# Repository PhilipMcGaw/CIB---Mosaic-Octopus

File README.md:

# CIB - Mosaic Octopus

Breakout board for Pico Technologies Ltd ADC20/ADC24 (https://www.picotech.com/accessories/data-logger-terminal-boards/adc-20-24-terminal-board)

> The ADC-20/ADC-24 Terminal Board is designed for use with the 8-channel ADC-20 and 16-channel ADC-24 High-Resolution Data Loggers. For simple applications, you can simply connect sensor wires to the screw terminals on the terminal board without the need for soldering. For more advanced applications, the terminal board enables you to design and build sensor circuits that condition measurements for the data loggers to process. The board has empty locations for extra components.

## Pinout

| DB 25 Pin (J1) | Function |
| --- | --- |
| 1  | Analogue Channel 2 |
| 2  | Analogue Channel 4 |
| 3  | Analogue Channel 6 |
| 4  | Analogue Channel 8 |
| 5  | Analogue Channel 10 |
| 6  | Analogue Channel 12 |
| 7  | Analogue Channel 14 |
| 8  | Analogue Channel 16 |
| 9  | Analogue Ground (AG) |
| 10 | +5 VDC |
| 11 | -5 VDC |
| 12 | +2V5 |
| 13 | DIO 4 |
| 14 | Analogue Channel 1 |
| 15 | Analogue Channel 3 |
| 16 | Analogue Channel 5 |
| 17 | Analogue Channel 7 |
| 18 | Analogue Channel 9 |
| 19 | Analogue Channel 11 |
| 20 | Analogue Channel 13 |
| 21 | Analogue Channel 15 |
| 22 | Digital Ground (DG) |
| 23 | DIO 1 |
| 24 | DIO 2 |
| 25 | DIO 3 |

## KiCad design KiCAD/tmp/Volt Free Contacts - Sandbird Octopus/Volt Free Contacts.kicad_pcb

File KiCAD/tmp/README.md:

# Cephalopds

## Breakout PCBs

| | Labjack T7 | DAQM901A (20 channel Mux) | DAQM903A (20 channel relay card) | DAQM907A (mutifucntion card) | DAQM908A (40 channel single ended mux) |
| ---- | ----- | ---- |-----| ------ | ----- | ----- | 
| Blanket Octopus -- DE9 Breakout PCB |
| Algae Octopus -- DA15 Breakout PCB | 1x |    |   | |  |
| Bimac Octopus - DB25 Breakout PCB | | 2x | 1x |  |  |
| Coconut Octopus - DC37 Breakout PCB | 1 x| | 1x | 1x | 2 x |
|Flapjack Octopus -- Labjack T7 Breakout | 1 x|

### Flapjack Octopus -- Labjack T7 Breakout

[Flapjack Octopus -- Labjack T7 Breakout](https://chargepoint.atlassian.net/wiki/spaces/EN/pages/5075305172/Labjack+T7+Breakout+-+Flapjack+Octopus)

This is a breakout PCB for a Labjack T7, with 2.5 mm pitch screw headers to allow for quick wiring to the breakout PCB.

  * Digital IO ports are 5 V tolerant, there is no additional protection on the PCB.
  * Digital IO on ports C, E, F and M each have an LED that illuminates when 5V DC is applied
  * Digital IO port F is also set up as eight relay outputs, allowing up to eight 12/24 V (separate power supply required) to be driven from the Labjack
  * Analogue in ports are taken via a potential divider to allow prescaling if required.
  * Additional terminals are available for 5V and Ground, as well as other pins, these are on the lower edge. 

### Blanket Octopus -- DE9 Breakout PCB

[Blanket Octopus - DE9 Breakout PCB](https://chargepoint.atlassian.net/wiki/spaces/EN/pages/5095228149/DE9+Breakout+PCB+-+Blanket+Octopus)

### Algae Octopus -- DA15 Breakout PCB

[Algae Octopus - DA15 Breakout PCB](https://chargepoint.atlassian.net/wiki/spaces/EN/pages/5095195307/DA15+Breakout+PCB+-+Algae+Octopus)

### Bimac Octopus -- DB25 Breakout PCB

[Bimac Octopus - DB25 Breakout PCB](https://chargepoint.atlassian.net/wiki/spaces/EN/pages/5094773639/DB25+Breakout+PCB+-+Bimac+Octopus)

This is the breakout for a DB25 D-type, two of these are used to interface with the DAQ970's DAQM901A module, and one for the DAQM903A card.

### Coconut Octopus -- DC37 Breakout PCB

[Coconut Octopus - DC37 Breakout PCB](https://chargepoint.atlassian.net/wiki/spaces/EN/pages/5094741845/DC37+Breakout+PCB+-+Coconut+Octopus)

This is the breakout for a DC37 D-type, two of these are used to interface with the DAQ970's DAQM908A module, one for the DAQM903A  and one for the DAQM907A card,

## Simulation PCBs

### Pygmy Octopus -- RTD Simulation

[Pygmy Octopus - RTD Simulator](https://chargepoint.atlassian.net/wiki/spaces/EN/pages/5094740380/PT100+Simulator+-+Pygmy+Octopus)

### Sandbird Octopus -- Volt Free Contacts

[Sandbird Octopus - Volt Free Contacts](https://chargepoint.atlassian.net/wiki/spaces/EN/pages/5095260299/Volt+Free+Contacts+-+Sandbird+Octopus)

### Star-Sucker Pygmy Octopus -- Fans, Pumps and other loads

[Star-Sucker Pygmy Octopus - Fans, Pumps and other loads](https://chargepoint.atlassian.net/wiki/spaces/EN/pages/5129112107/Fans+Pumps+and+other+loads+-+Star-Sucker+Pygmy+Octopus)

### Blanket Octopus -- Relay / Contactor board

[Blanket Octopus -- Relay / Contactor board](https://chargepoint.atlassian.net/wiki/spaces/EN/pages/5129242298/Relay+Contactor+board+-+Blanket+Octopus)

--

Giant Pacific Octopus
Dumbo Octopus
California Two-Spot Octopus

Mimic Octopus
[Atlantic] Pygmy Octopus
Common Octopus

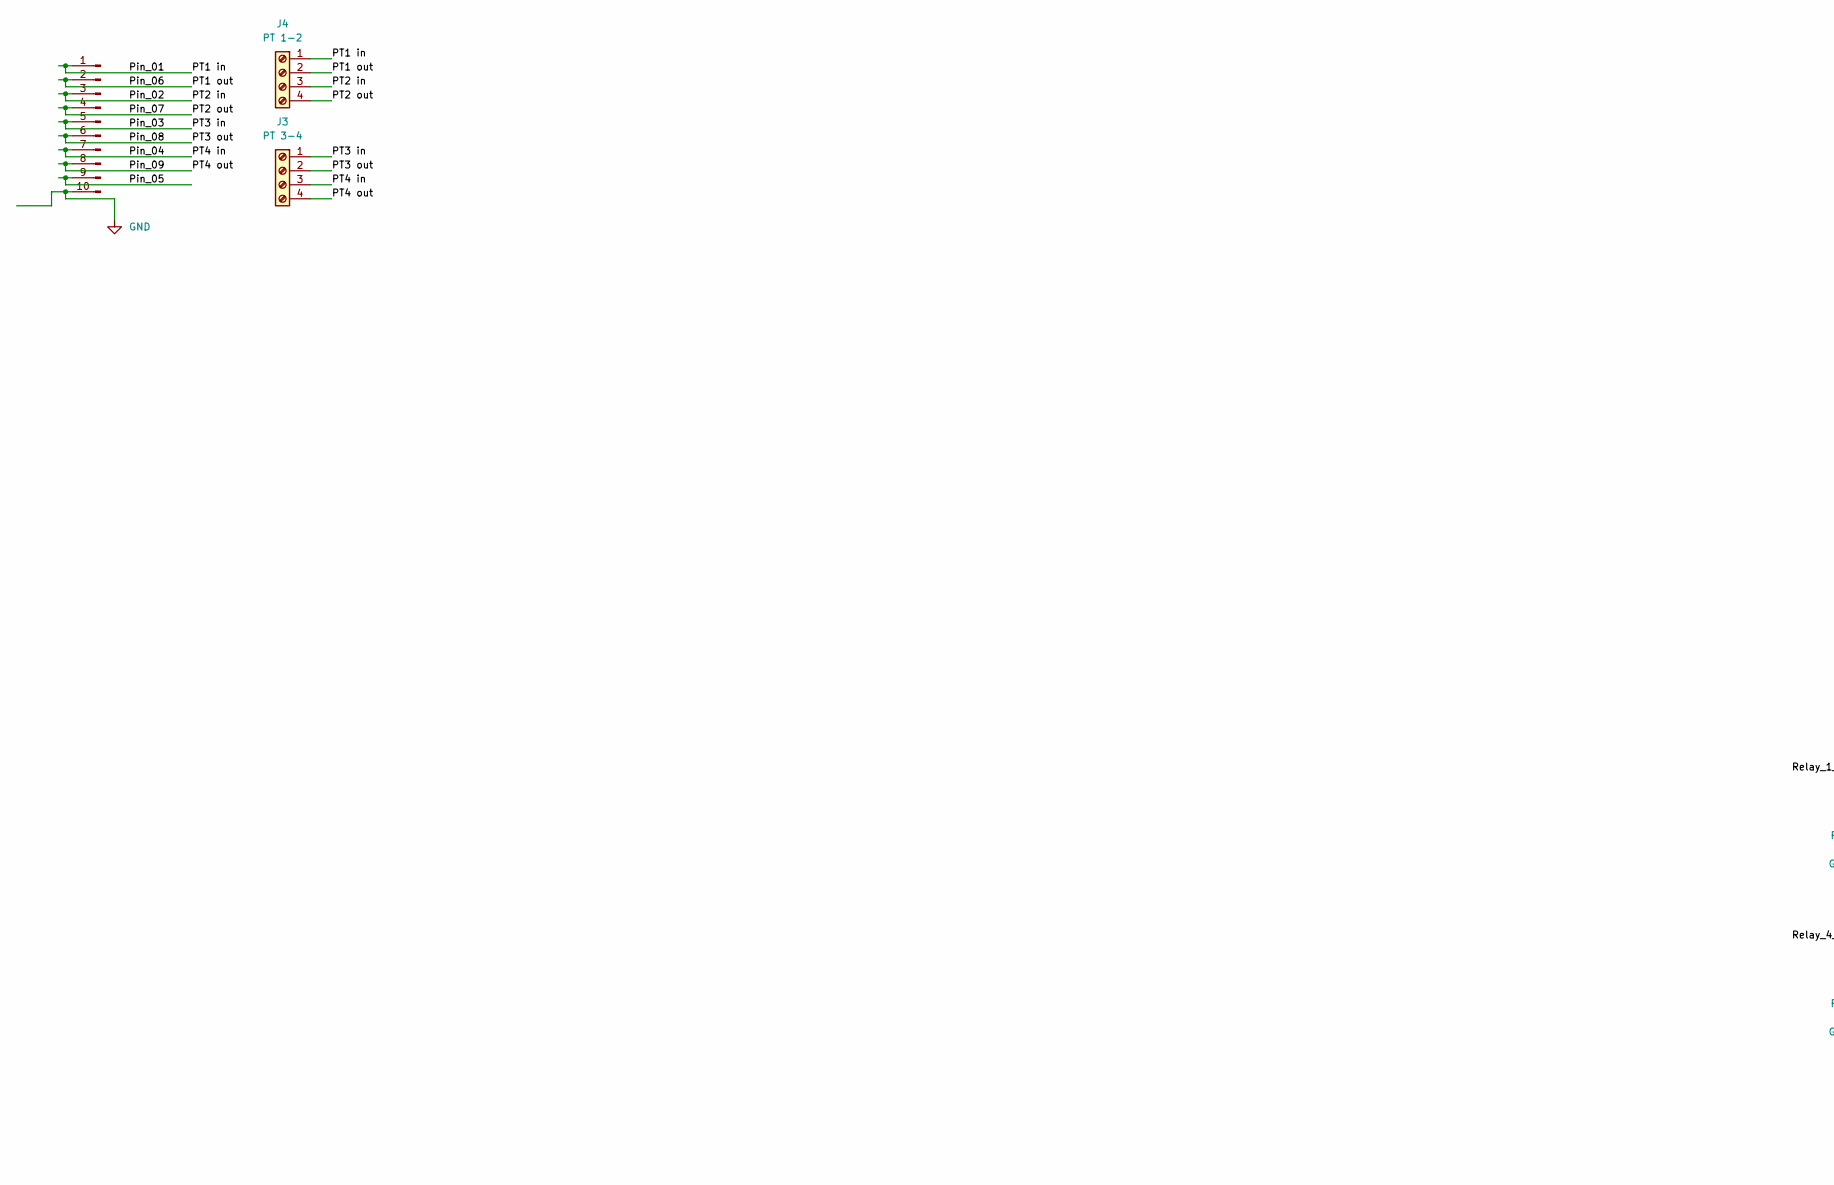
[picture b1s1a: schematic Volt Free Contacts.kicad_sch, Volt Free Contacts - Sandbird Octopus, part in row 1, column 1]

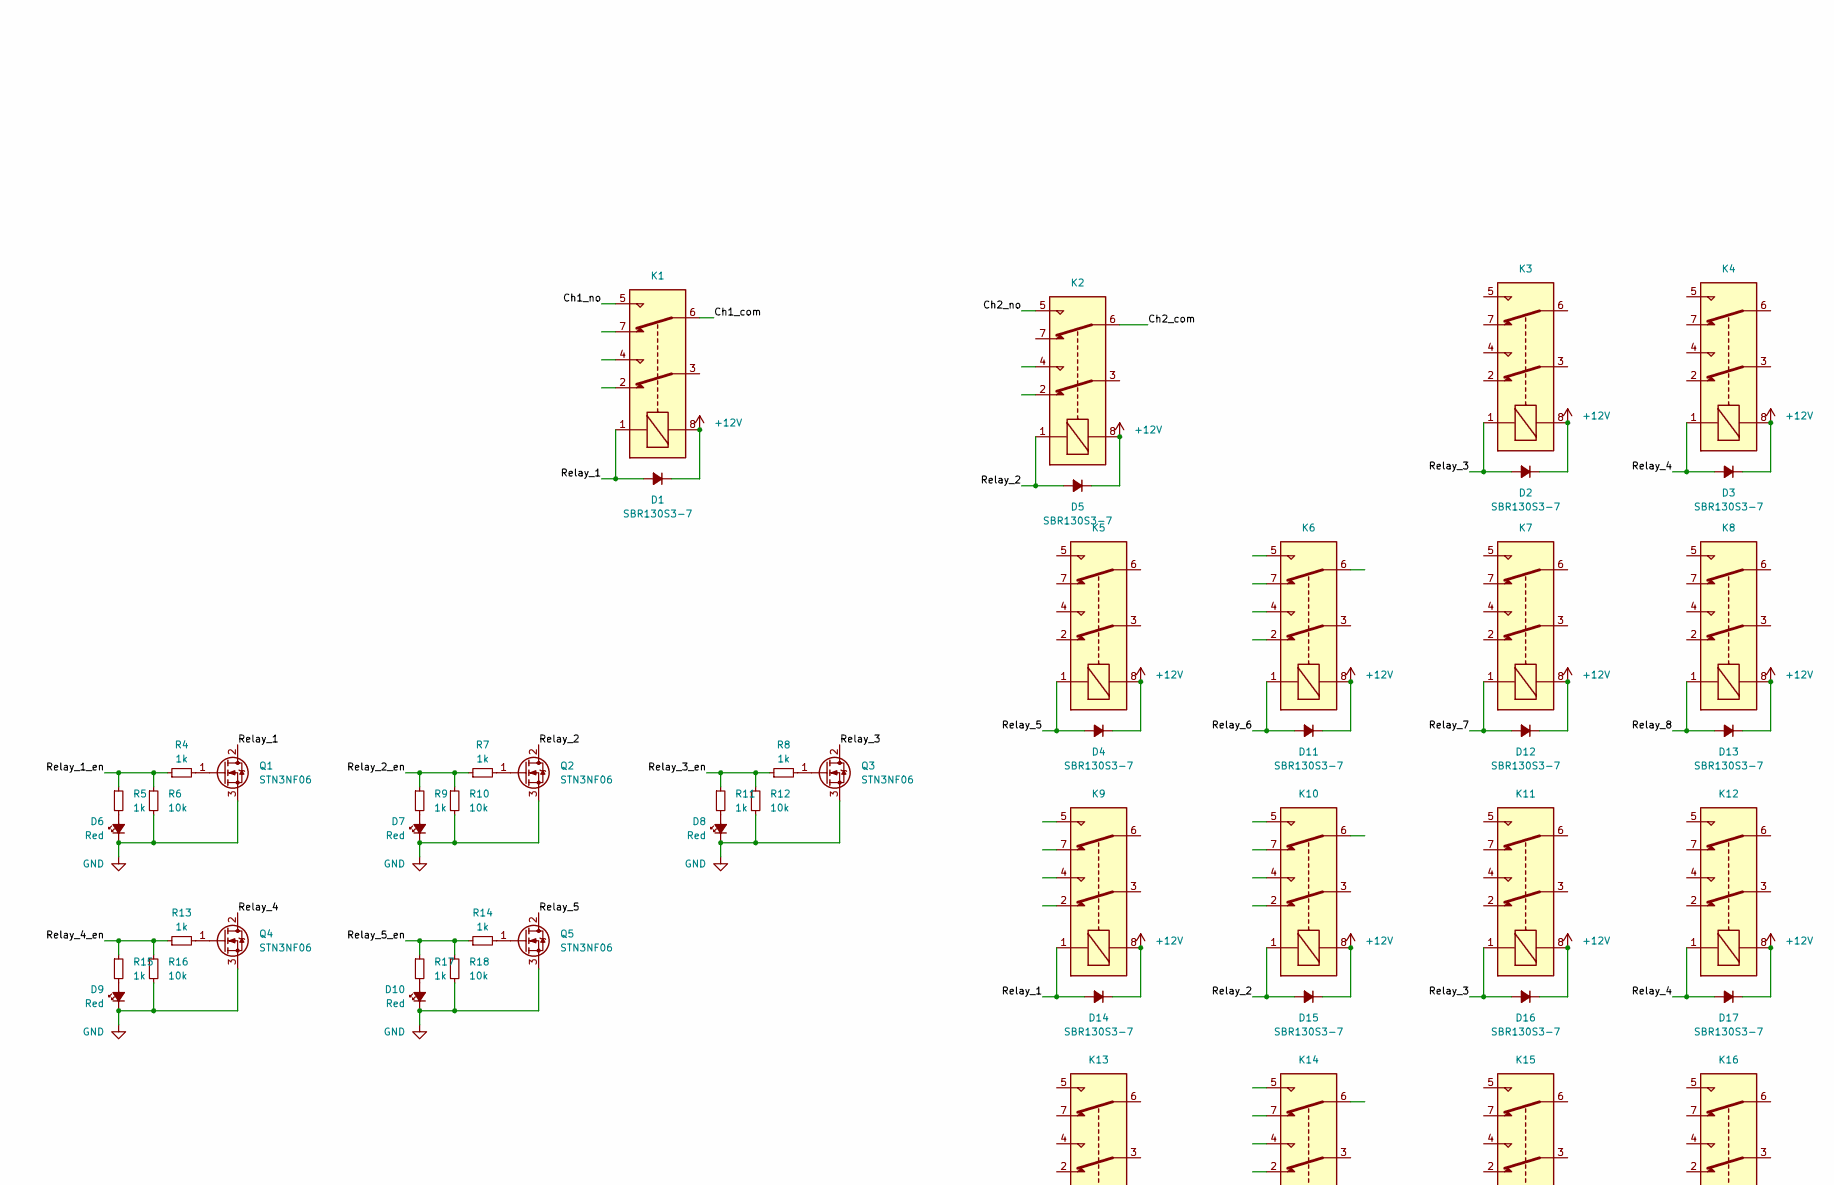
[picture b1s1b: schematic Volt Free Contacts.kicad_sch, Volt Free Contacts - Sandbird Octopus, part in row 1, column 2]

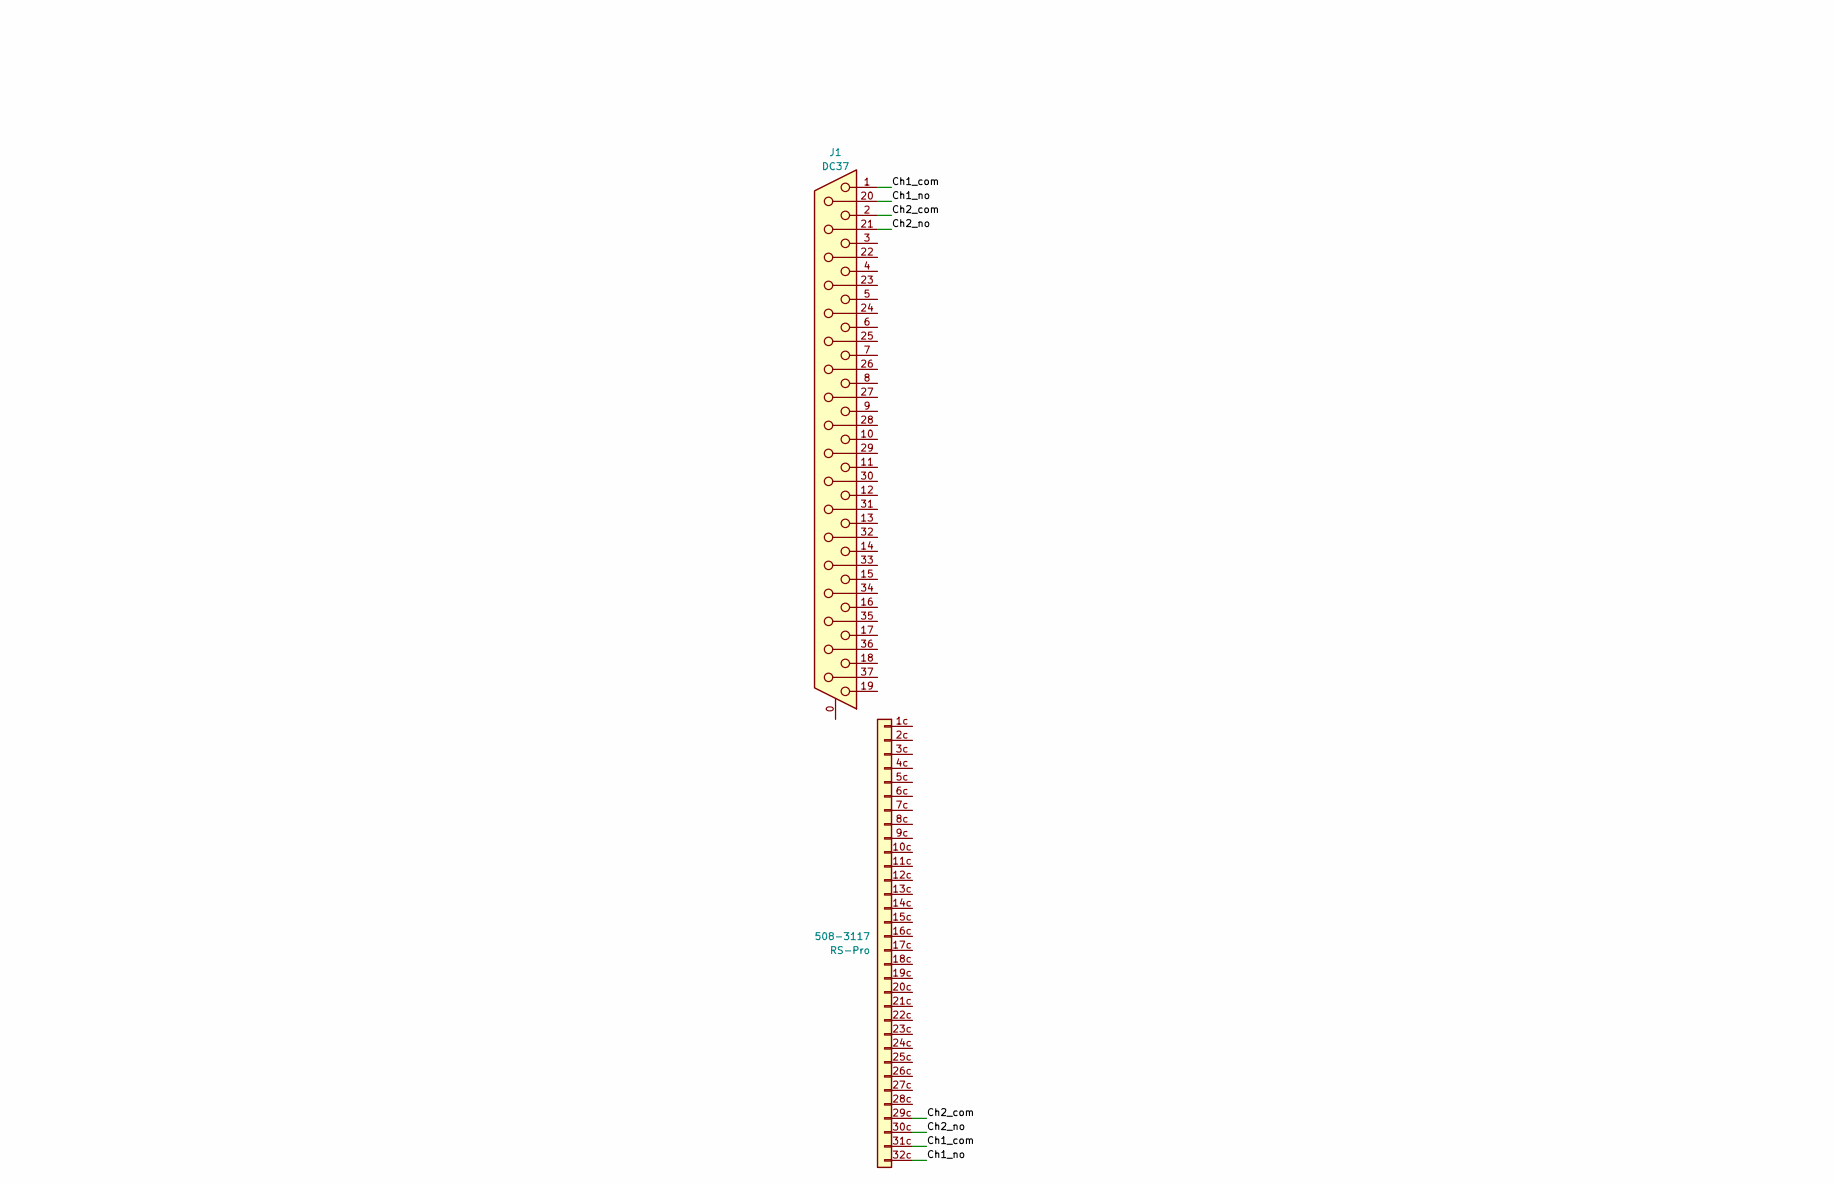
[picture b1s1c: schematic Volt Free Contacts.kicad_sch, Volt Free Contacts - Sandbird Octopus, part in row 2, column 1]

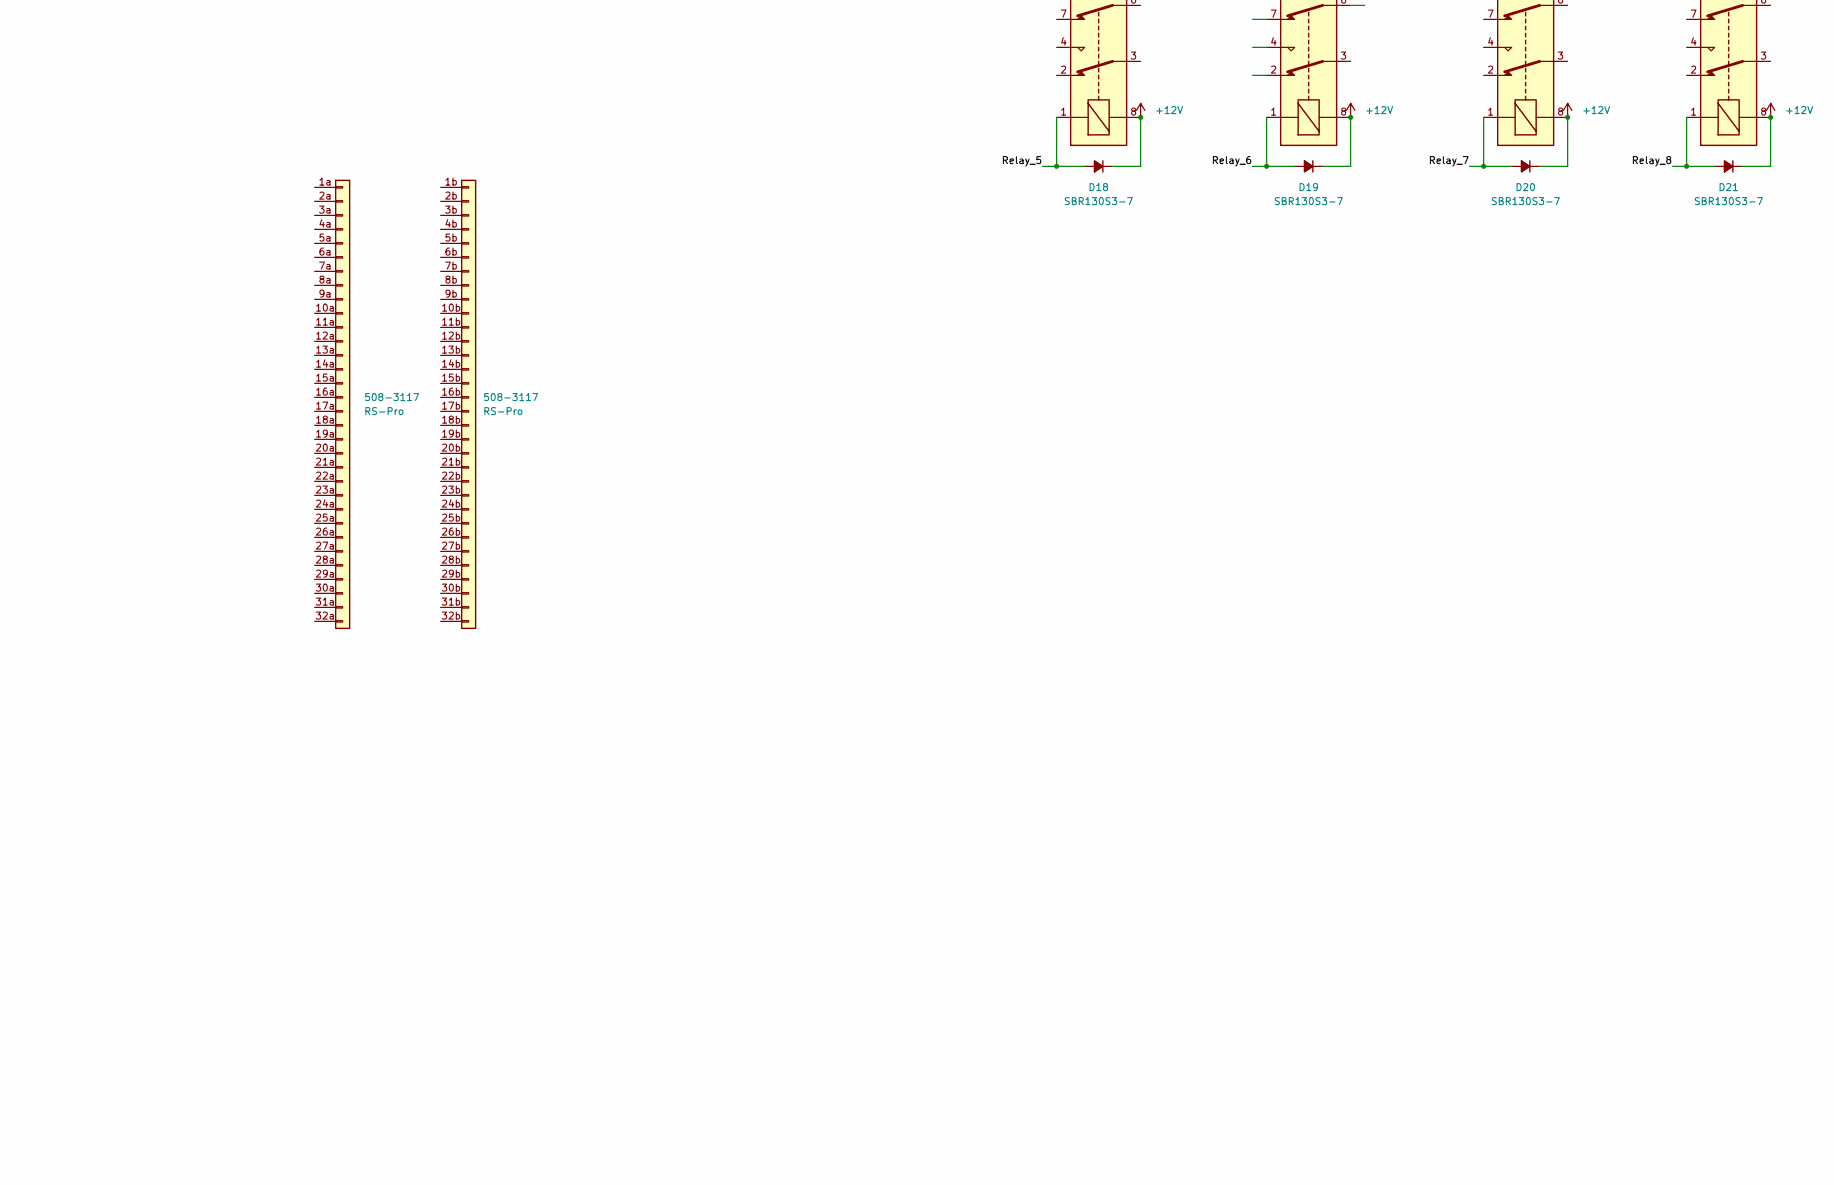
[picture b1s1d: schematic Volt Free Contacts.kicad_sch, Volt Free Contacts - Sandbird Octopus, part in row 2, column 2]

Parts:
D1, D2, D3, D4, D5, D11, D12, D13, D14, D15, D16, D17, D18, D19, D20, D21: SBR130S3-7; D_SOD-323_HandSoldering
D6, D7, D8, D9, D10: Red; LED_0805_2012Metric_Pad1.15x1.40mm_HandSolder
J1: DC37; DSUB-37_Female_Horizontal_P2.77x2.84mm_EdgePinOffset9.90mm_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
J3: PT 3-4; TerminalBlock_Phoenix_MPT-0,5-4-2.54_1x04_P2.54mm_Horizontal
J4: PT 1-2; TerminalBlock_Phoenix_MPT-0,5-4-2.54_1x04_P2.54mm_Horizontal
J6: Pin Header; PinHeader_2x05_P2.54mm_Vertical
J7: 03x32_DIN41612; Eurocard; Manufacture PartNumber 508-3117
K1, K2, K3, K4, K5, K6, K7, K8, K9, K10, K11, K12, K13, K14, K15, K16: Relay_DPDT_Omron_G6K-2P; Manufacturer # G6K-2P DC12; DigiKey # Z117-ND
Q1, Q2, Q3, Q4, Q5: STN3NF06; SOT-223-3_TabPin2
R4, R5, R7, R8, R9, R11, R13, R14, R15, R17: 1k; R_0805_2012Metric_Pad1.20x1.40mm_HandSolder
R6, R10, R12, R16, R18: 10k; R_0805_2012Metric_Pad1.20x1.40mm_HandSolder

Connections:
+12V: D1.1 (K), D2.1 (K), D3.1 (K), D4.1 (K), D5.1 (K), D11.1 (K), D12.1 (K), D13.1 (K), D14.1 (K), D15.1 (K), D16.1 (K), D17.1 (K), D18.1 (K), D19.1 (K), D20.1 (K), D21.1 (K), K1.8, K2.8, K3.8, K4.8, K5.8, K6.8, K7.8, K8.8, K9.8, K10.8, K11.8, K12.8, K13.8, K14.8, K15.8, K16.8
/Ch1_com: J1.1, J7.31c (Pin_31), K1.6
/Ch1_no: J1.20, J7.32c (Pin_32), K1.5
/Ch2_com: J1.2, J7.29c (Pin_29), K2.6
/Ch2_no: J1.21, J7.30c (Pin_30), K2.5
/PT1 in: J4.1, J6.1
/PT1 out: J4.2, J6.2
/PT2 in: J4.3, J6.3
/PT2 out: J4.4, J6.4
/PT3 in: J3.1, J6.5
/PT3 out: J3.2, J6.6
/PT4 in: J3.3, J6.7
/PT4 out: J3.4, J6.8
/Pin_05: J6.9
/Relay_1: D1.2 (A), D14.2 (A), K1.1, K9.1, Q1.2 (D)
/Relay_1_en: R4.1, R5.1, R6.1
/Relay_2: D5.2 (A), D15.2 (A), K2.1, K10.1, Q2.2 (D)
/Relay_2_en: R7.1, R9.1, R10.1
/Relay_3: D2.2 (A), D16.2 (A), K3.1, K11.1, Q3.2 (D)
/Relay_3_en: R8.1, R11.1, R12.1
/Relay_4: D3.2 (A), D17.2 (A), K4.1, K12.1, Q4.2 (D)
/Relay_4_en: R13.1, R15.1, R16.1
/Relay_5: D4.2 (A), D18.2 (A), K5.1, K13.1, Q5.2 (D)
/Relay_5_en: R14.1, R17.1, R18.1
/Relay_6: D11.2 (A), D19.2 (A), K6.1, K14.1
/Relay_7: D12.2 (A), D20.2 (A), K7.1, K15.1
/Relay_8: D13.2 (A), D21.2 (A), K8.1, K16.1
GND: D6.1 (K), D7.1 (K), D8.1 (K), D9.1 (K), D10.1 (K), J6.10, Q1.3 (S), Q2.3 (S), Q3.3 (S), Q4.3 (S), Q5.3 (S), R6.2, R10.2, R12.2, R16.2, R18.2
unnamed: D6.2 (A), R5.2
unnamed: D7.2 (A), R9.2
unnamed: D8.2 (A), R11.2
unnamed: D9.2 (A), R15.2
unnamed: D10.2 (A), R17.2
unnamed: Q1.1 (G), R4.2
unnamed: Q2.1 (G), R7.2
unnamed: Q3.1 (G), R8.2
unnamed: Q4.1 (G), R13.2
unnamed: Q5.1 (G), R14.2

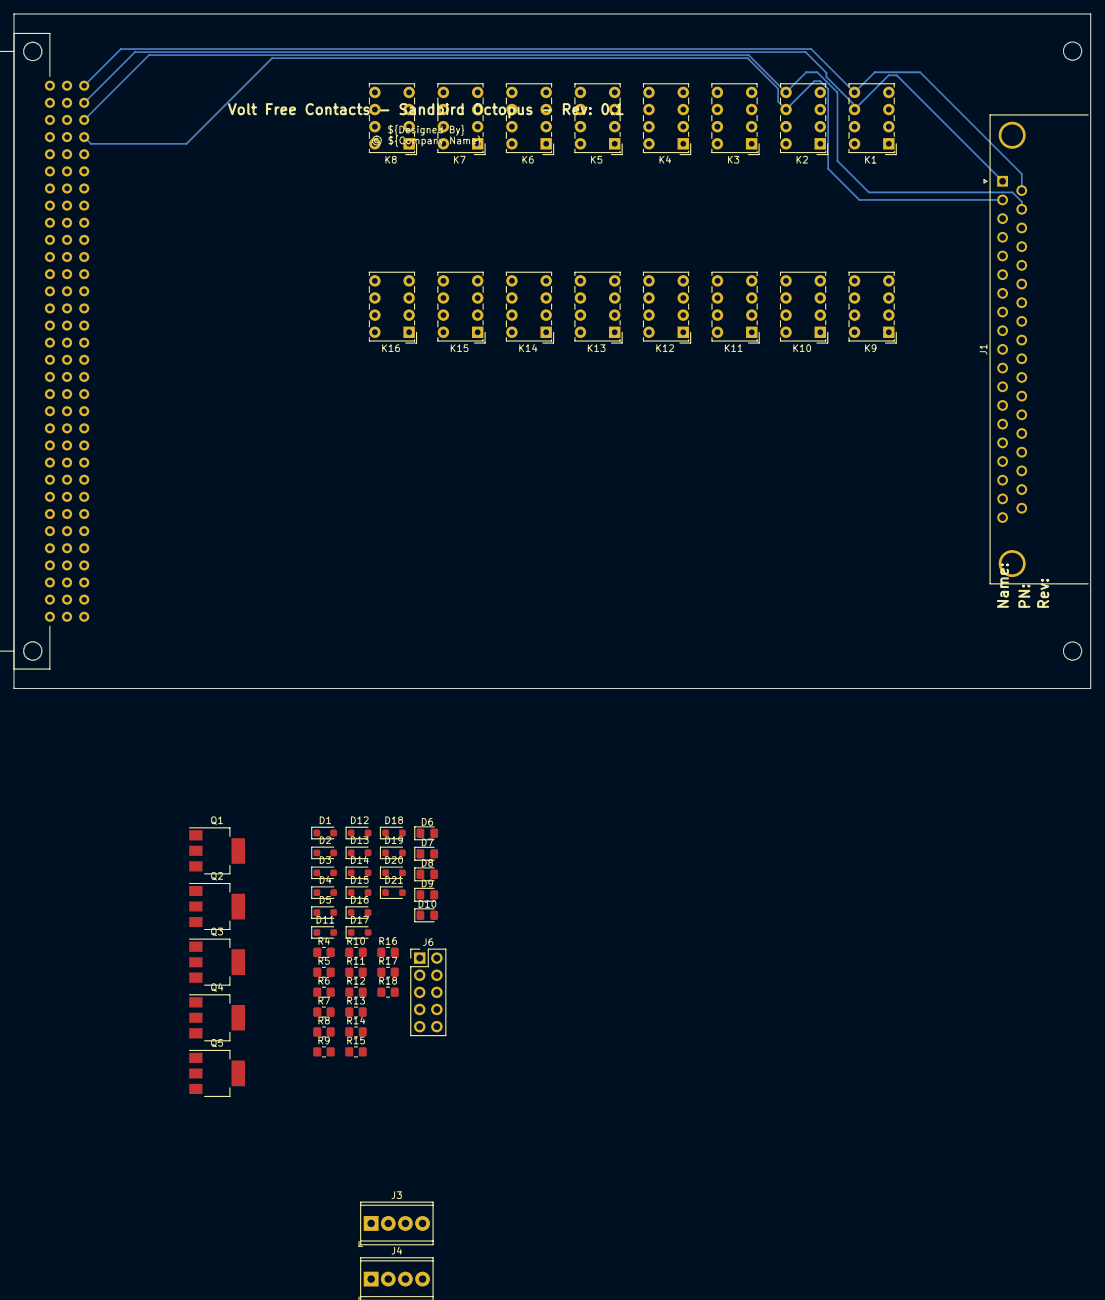
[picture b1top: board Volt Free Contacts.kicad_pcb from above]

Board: 2 copper layers, 159.6 x 100.0 mm, 62 parts (0 on the bottom side), 37 nets.

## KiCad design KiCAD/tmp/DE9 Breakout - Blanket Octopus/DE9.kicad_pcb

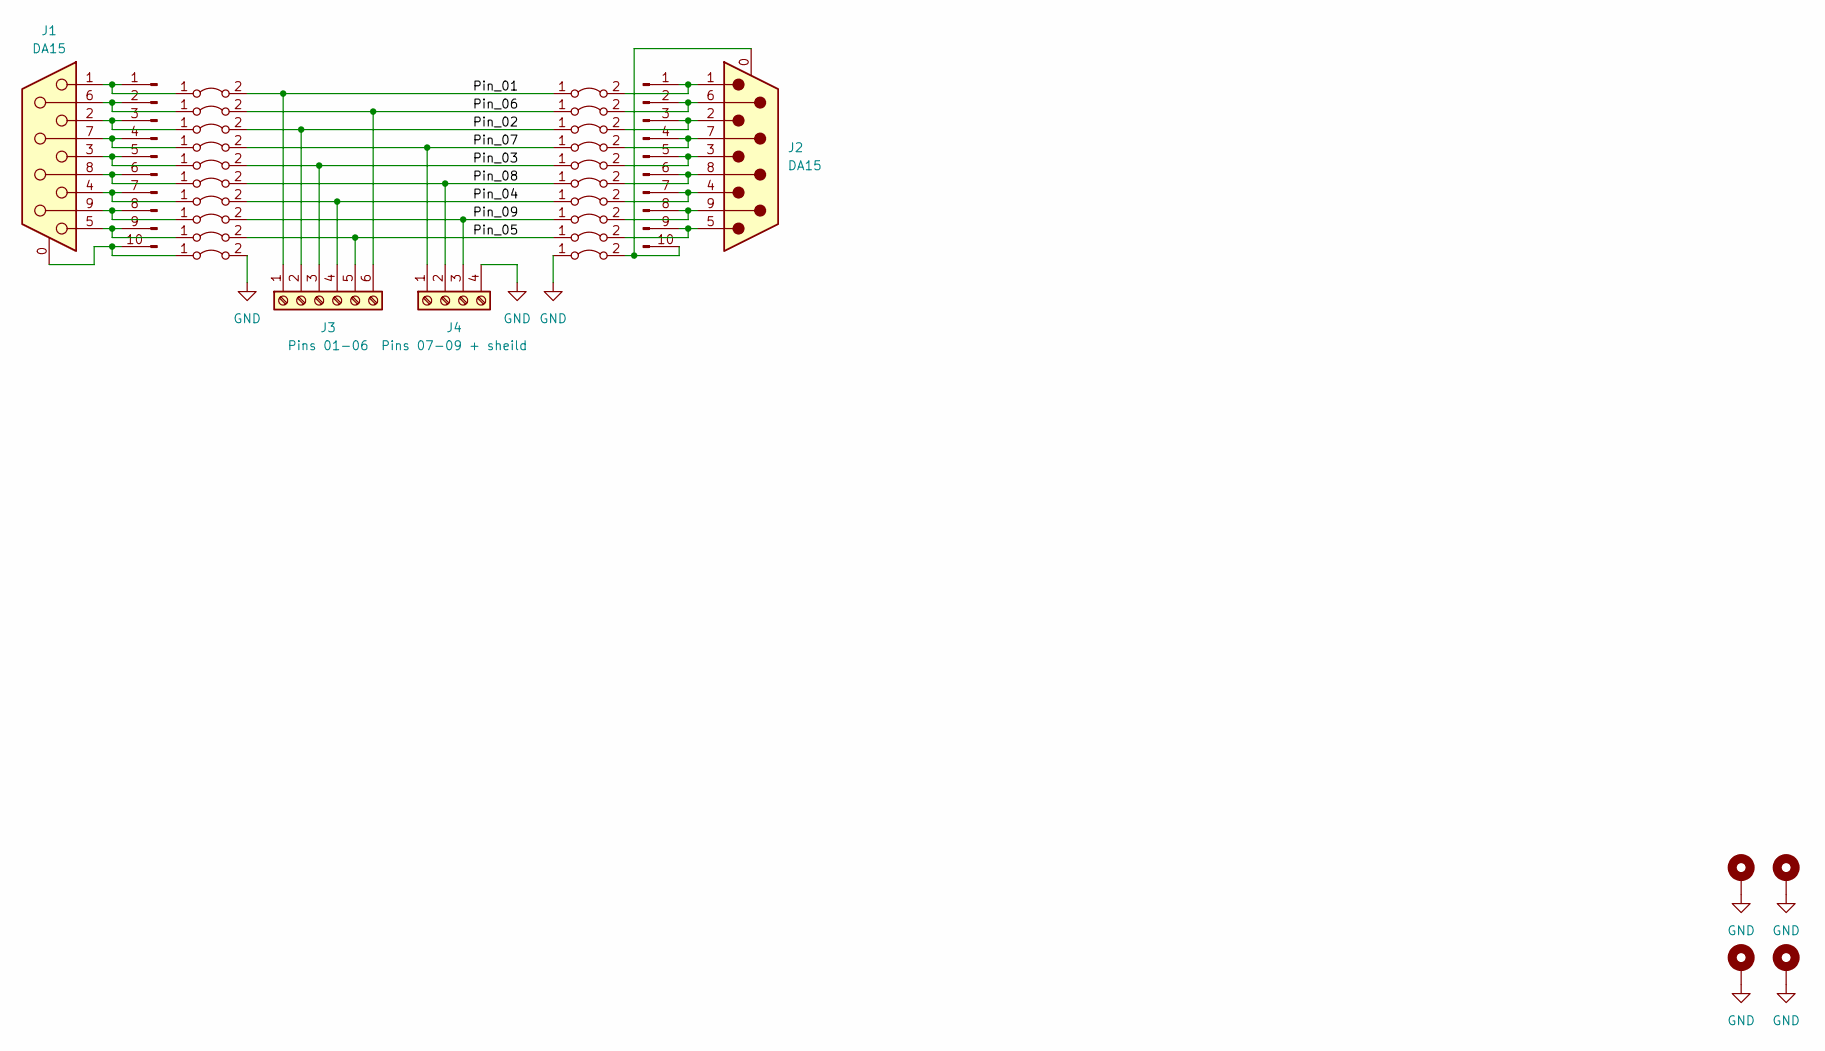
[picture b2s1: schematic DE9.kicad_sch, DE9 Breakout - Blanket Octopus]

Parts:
H1, H2, H3, H4: MountingHole; MountingHole_3.5mm_Pad
J1: DA15; DSUB-9_Female_Horizontal_P2.77x2.84mm_EdgePinOffset7.70mm_H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
J2: DA15; DSUB-9_Male_Horizontal_P2.77x2.84mm_EdgePinOffset7.70mm_Hou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
J3: Pins 01-06; TerminalBlock_Phoenix_MPT-0,5-6-2.54_1x06_P2.54mm_Horizontal
J4: Pins 07-09 + sheild; TerminalBlock_Phoenix_MPT-0,5-4-2.54_1x04_P2.54mm_Horizontal
J6, J8: Pin Header; PinHeader_2x05_P2.54mm_Vertical
JP1, JP5: Pin_01; SolderJumper-2_P1.3mm_Bridged_RoundedPad1.0x1.5mm
JP2, JP7: Pin_14; SolderJumper-2_P1.3mm_Bridged_RoundedPad1.0x1.5mm
JP3, JP52: Sheild; SolderJumper-2_P1.3mm_Bridged_RoundedPad1.0x1.5mm
JP4, JP9: Pin_02; SolderJumper-2_P1.3mm_Bridged_RoundedPad1.0x1.5mm
JP6, JP11: Pin_15; SolderJumper-2_P1.3mm_Bridged_RoundedPad1.0x1.5mm
JP8, JP13: Pin_03; SolderJumper-2_P1.3mm_Bridged_RoundedPad1.0x1.5mm
JP10, JP15: Pin_16; SolderJumper-2_P1.3mm_Bridged_RoundedPad1.0x1.5mm
JP12, JP17: Pin_04; SolderJumper-2_P1.3mm_Bridged_RoundedPad1.0x1.5mm
JP14, JP19: Pin_17; SolderJumper-2_P1.3mm_Bridged_RoundedPad1.0x1.5mm
JP16, JP21: Pin_05; SolderJumper-2_P1.3mm_Bridged_RoundedPad1.0x1.5mm

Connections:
/Pin_01: J3.1, JP1.2 (B), JP5.1 (A)
/Pin_02: J3.2, JP4.2 (B), JP9.1 (A)
/Pin_03: J3.3, JP8.2 (B), JP13.1 (A)
/Pin_04: J3.4, JP12.2 (B), JP17.1 (A)
/Pin_05: J3.5, JP16.2 (B), JP21.1 (A)
/Pin_06: J3.6, JP2.2 (B), JP7.1 (A)
/Pin_07: J4.1, JP6.2 (B), JP11.1 (A)
/Pin_08: J4.2, JP10.2 (B), JP15.1 (A)
/Pin_09: J4.3, JP14.2 (B), JP19.1 (A)
GND: H1.1, H2.1, H3.1, H4.1, J4.4, JP3.1 (A), JP52.2 (B)
unnamed: J1.0 (PAD), J6.10, JP52.1 (A)
unnamed: J2.0 (PAD), J8.10, JP3.2 (B)
unnamed: J1.1, J6.1, JP1.1 (A)
unnamed: J1.6, J6.2, JP2.1 (A)
unnamed: J1.2, J6.3, JP4.1 (A)
unnamed: J1.7, J6.4, JP6.1 (A)
unnamed: J1.3, J6.5, JP8.1 (A)
unnamed: J1.8, J6.6, JP10.1 (A)
unnamed: J1.4, J6.7, JP12.1 (A)
unnamed: J1.9, J6.8, JP14.1 (A)
unnamed: J1.5, J6.9, JP16.1 (A)
unnamed: J2.1, J8.1, JP5.2 (B)
unnamed: J2.6, J8.2, JP7.2 (B)
unnamed: J2.2, J8.3, JP9.2 (B)
unnamed: J2.7, J8.4, JP11.2 (B)
unnamed: J2.3, J8.5, JP13.2 (B)
unnamed: J2.8, J8.6, JP15.2 (B)
unnamed: J2.4, J8.7, JP17.2 (B)
unnamed: J2.9, J8.8, JP19.2 (B)
unnamed: J2.5, J8.9, JP21.2 (B)

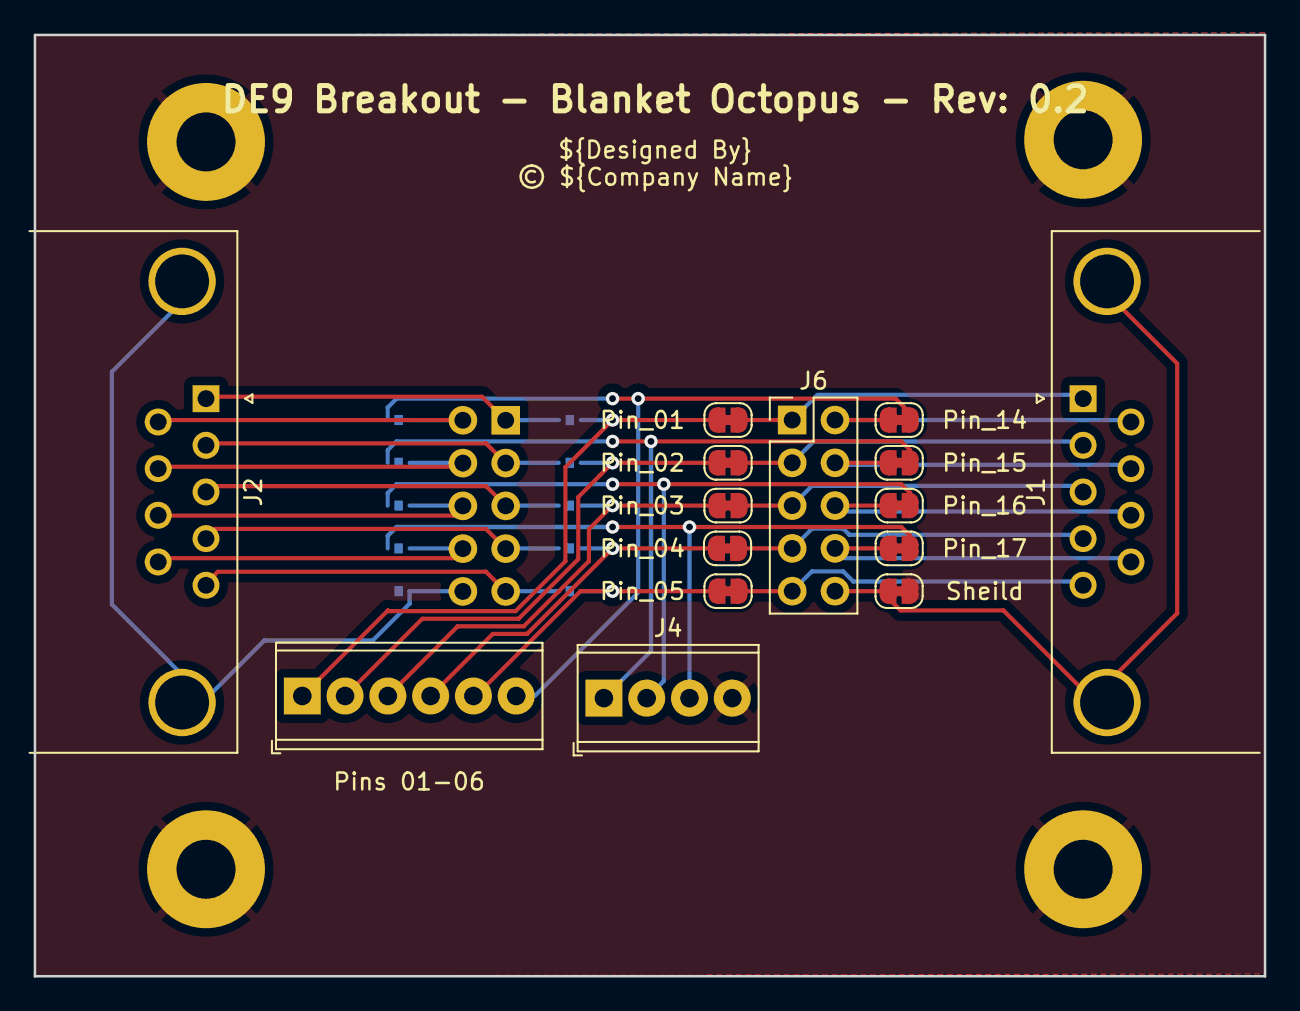
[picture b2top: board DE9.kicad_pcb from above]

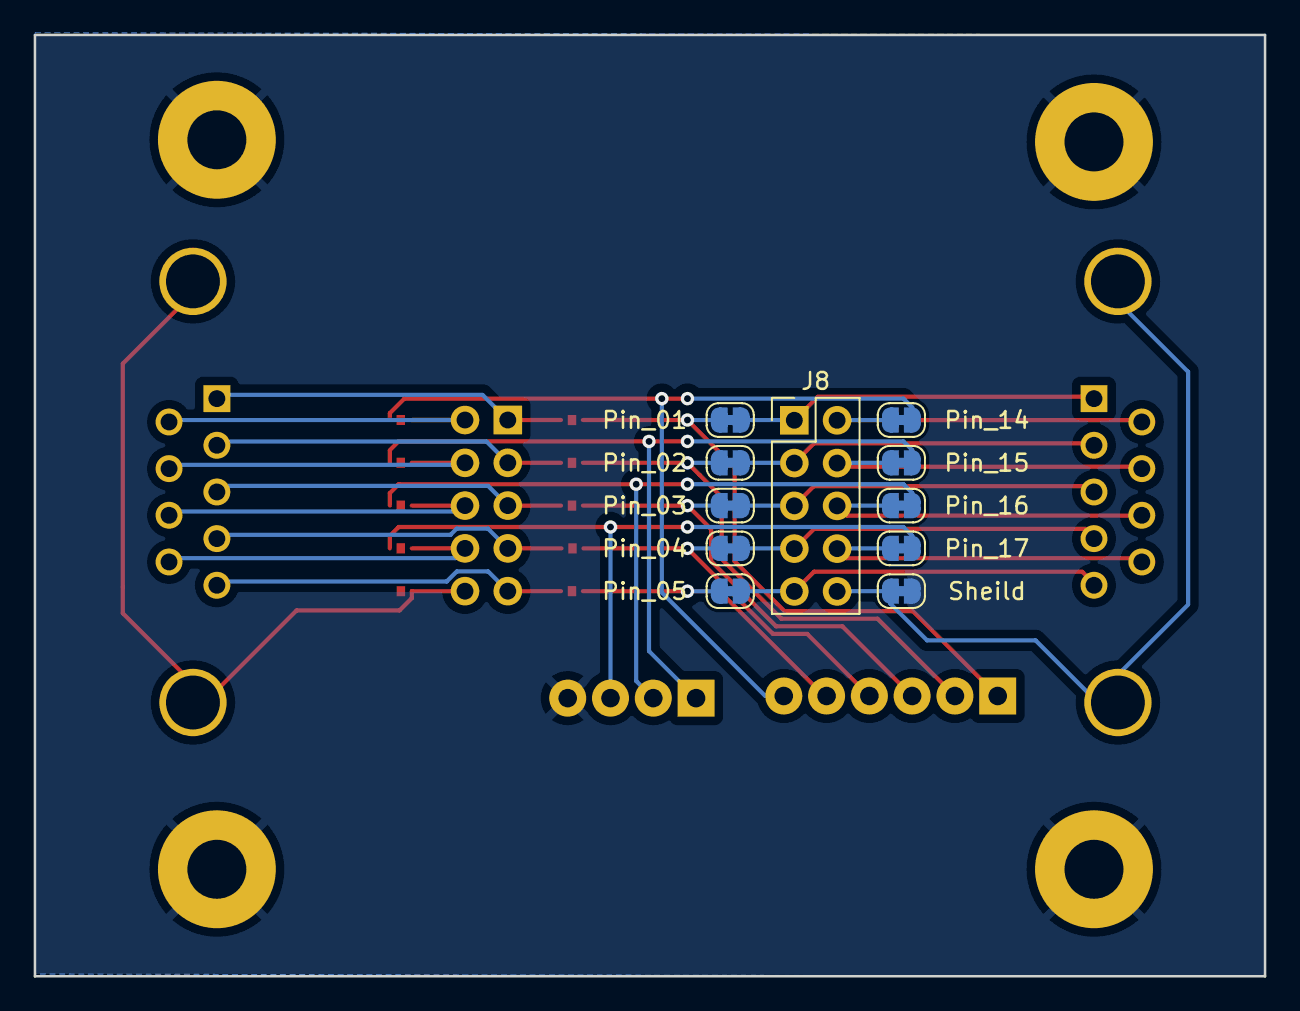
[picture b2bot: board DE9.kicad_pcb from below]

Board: 2 copper layers, 73.0 x 55.9 mm, 30 parts (11 on the bottom side), 30 nets.
